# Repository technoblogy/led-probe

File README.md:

# LED Probe
A simple LED tester that provides a convenient way of testing most types of through-hole or surface-mount LEDs.

For more information see <http://www.technoblogy.com/show?53Z6>.

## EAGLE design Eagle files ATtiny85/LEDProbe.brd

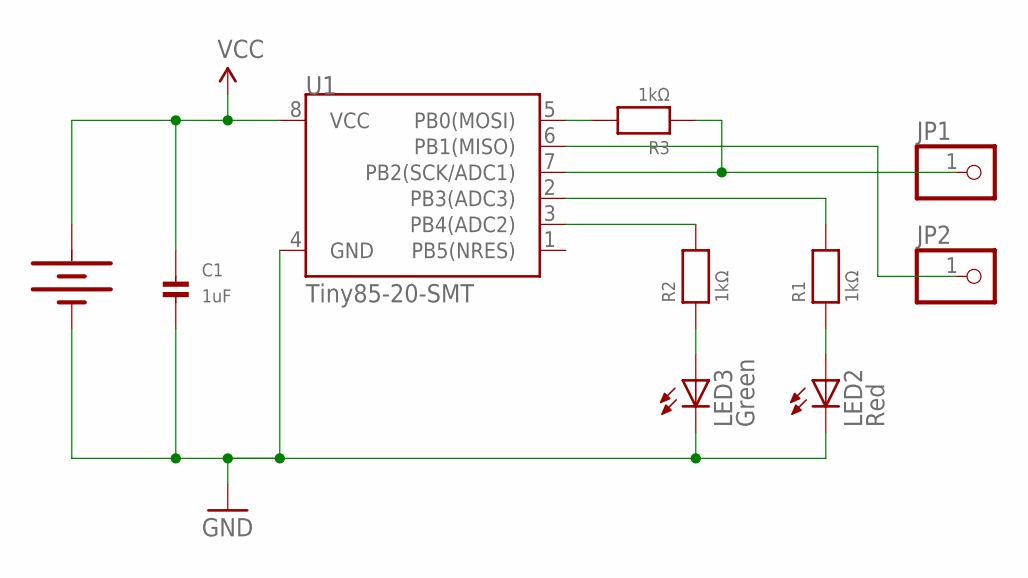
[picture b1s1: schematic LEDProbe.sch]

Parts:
BAT2: 20mm coincell; BATTCON_20MM_4LEGS
C1: 1uF; _0805MP
JP1, JP2: PINHD-1X1CB; 1X01-CLEANBIG
LED2: Red; CHIPLED_0805
LED3: Green; CHIPLED_0805
R1, R2, R3: 1kΩ; _0805MP
U1: Tiny85-20-SMT; SO08-EIAJ

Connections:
GND: BAT2.NEGATIVE (-), C1.2, LED2.C, LED3.C, U1.4 (GND)
unnamed: JP2.1, U1.6 (PB1(MISO))
unnamed: LED3.A, R2.1
unnamed: R1.2, U1.2 (PB3(ADC3))
unnamed: LED2.A, R1.1
unnamed: JP1.1, R3.1, U1.7 (PB2(SCK/ADC1))
unnamed: R2.2, U1.3 (PB4(ADC2))
unnamed: R3.2, U1.5 (PB0(MOSI))
VCC: BAT2.POSITIVE@1 (+), BAT2.POSITIVE@2 (+), BAT2.POSITIVE@3 (+), BAT2.POSITIVE@4 (+), C1.1, U1.8 (VCC)

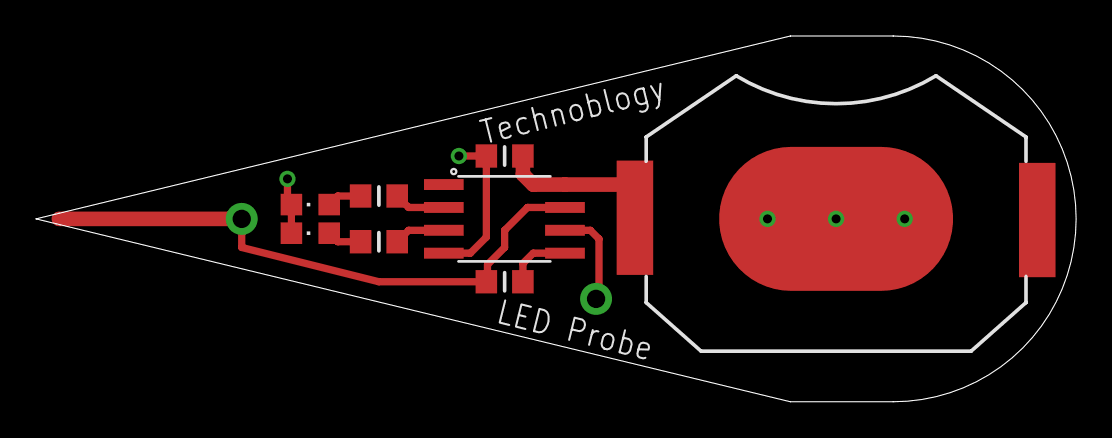
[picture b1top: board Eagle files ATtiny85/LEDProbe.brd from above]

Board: 2 copper layers, 57.8 x 20.3 mm, 10 parts (0 on the bottom side), 9 nets.

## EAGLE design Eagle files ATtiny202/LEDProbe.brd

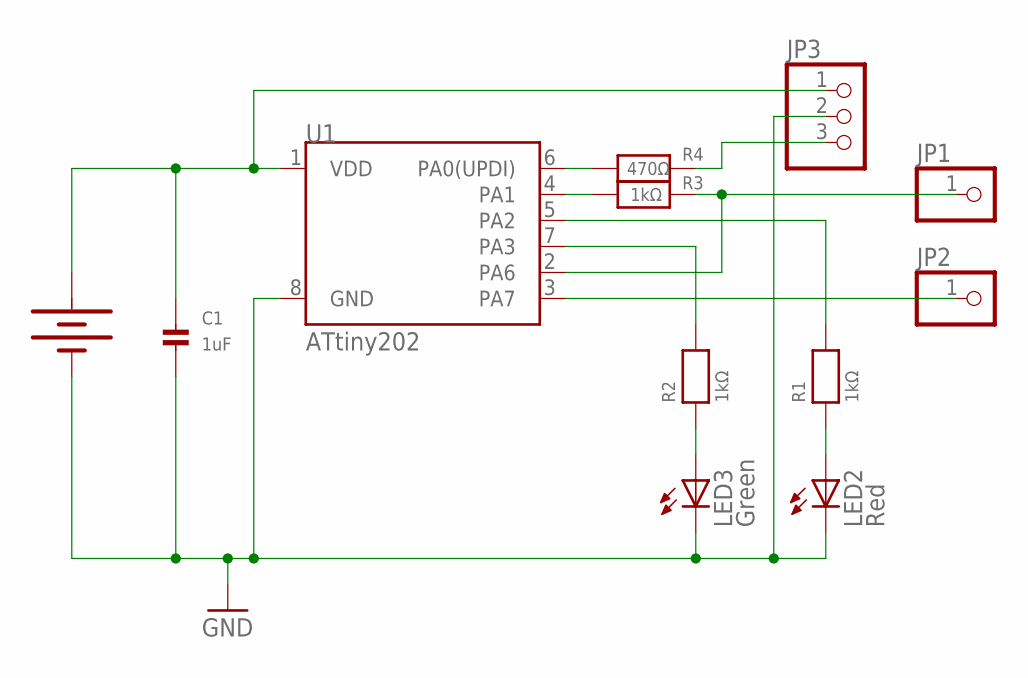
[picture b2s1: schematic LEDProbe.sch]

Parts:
BAT2: 20mm coincell; BATTCON_20MM_4LEGS
C1: 1uF; _0805MP
JP1, JP2: PINHD-1X1CB; 1X01-CLEANBIG
JP3: PINHD-1X3CB; 1X03-CLEANBIG
LED2: Red; CHIPLED_0805
LED3: Green; CHIPLED_0805
R1, R2, R3: 1kΩ; _0805MP
R4: 470Ω; _0805MP
U1: ATtiny202; SO08-EIAJ

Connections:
GND: BAT2.NEGATIVE (-), C1.2, JP3.2, LED2.C, LED3.C, U1.8 (GND)
unnamed: JP2.1, U1.3 (PA7)
unnamed: R4.2, U1.6 (PA0(UPDI))
unnamed: LED3.A, R2.1
unnamed: R1.2, U1.5 (PA2)
unnamed: LED2.A, R1.1
unnamed: JP1.1, R3.1, U1.2 (PA6)
unnamed: R2.2, U1.7 (PA3)
unnamed: R3.2, U1.4 (PA1)
unnamed: JP3.3, R4.1
unnamed: BAT2.POSITIVE@1 (+), BAT2.POSITIVE@2 (+), BAT2.POSITIVE@3 (+), BAT2.POSITIVE@4 (+), C1.1, JP3.1, U1.1 (VDD)

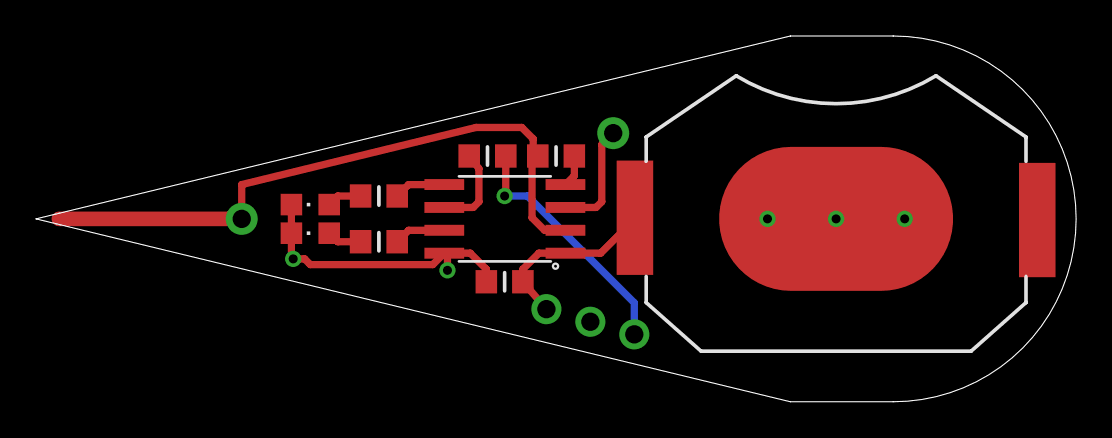
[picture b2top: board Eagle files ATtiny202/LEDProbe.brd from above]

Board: 2 copper layers, 57.8 x 20.3 mm, 12 parts (0 on the bottom side), 11 nets.

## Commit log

2025-05-20 Version 1 - 20th May 2025

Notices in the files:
parts and their libraries:
microbuilder: This work is placed in the public domain, and may be freely used for commercial and non-commercial work with the following conditions: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
SparkFun-Electromechanical: Licensing: Creative Commons ShareAlike 4.0 International - https://creativecommons.org/licenses/by-sa/4.0
